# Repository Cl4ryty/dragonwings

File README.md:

# dragonwings
An ergonomic unibody split keyboard made for steno.

- key layout generated using 
- PCB design in KiCad
- uses  with 

## Features:
- for Pro Micro or compatible controllers
- choc spacing (for choc v1 switches)
- pcb backplate with holes for rubber feet and threaded insert – allows usage on desks as well as tripod mounting the keyboard
- approximate size: 31 x 11 x 2 cm
- 30 keys
  - 15 keys on each side
  - 3 thumb keys per side
  - for steno this means: 
    - 2 thumber keys (one per side)
    - split S and *: 2 S keys 4 * keys (2 per side)
    - 2 extra keys on the left, can be set arbitarily in firmware – for eample to switch between layers or used as modifier keys

## The built keyboard

### parts used:
- dragonwings pcb & backplate
- 30 pink choc switches (linear 20gf)
- 30 MCC keycaps
- Pro Micro
- 5 through hole rubber feet, 5mm diameter (search for glass table top spacers)
- 1 UNC 1/4" hex nut 
- 7 M2x5mm standoffs
- 14 M2x4mm screws
- 1 SMD button, 5x5x2mm
- 30 SMD diodes (1N4148W, SOD-123)

## repository file structure
- 
- `pretty_pictures` contains renders and images of the built keyboard
- `dragonwings_backplate` contains KiCAD files for the backplate as well as the gebers 
  – the dagonwings_backplate_gerbers are tested but are missing a hole for the 5th rubber foot without which the board is not stable on a flat surface
  – the dragonwings_backplate_gerbers_updated are genreated from the updated kicad files and contain the additional hole for the 5th foot – these have not been tested but should work and one then would not have to drill the hole manually
- the dragonwings kicad files are contained in the root directory and the corresponding gerbers (tested and working) are in the `dragonwings_gerbers` directory, also available as a zip archive
- `compiled firmware` contains compiled firmware without or with first-up chord-send and tap-and-hold chord repeat – they contain two layers, one steno layer using GeminiPR and a qwerty steno layer which can be toggled with the lower key of the leftmost column
- firmware files to modify and compile yourself are available [here](https://github.com/Cl4ryty/qmk-steno-extensions/tree/dragonwings/keyboards/dragonwings) (1up and repeat) and [here](https://github.com/Cl4ryty/qmk_firmware/tree/dragonwings/keyboards/dragonwings) (just QMK without steno extensions)

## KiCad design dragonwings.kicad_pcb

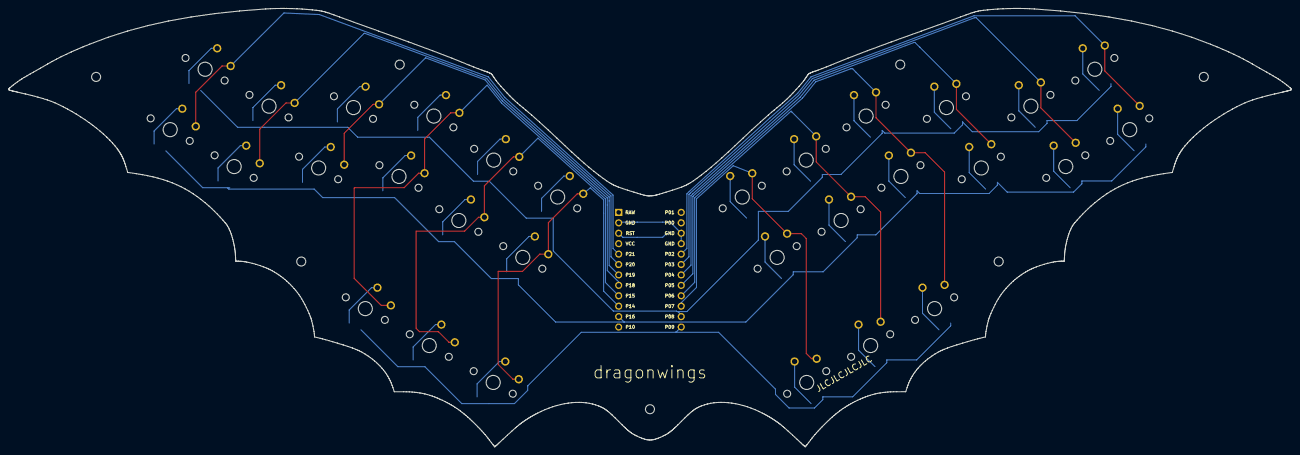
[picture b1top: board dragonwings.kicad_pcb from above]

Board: 2 copper layers, 312.8 x 106.9 mm, 69 parts (1 on the bottom side), 47 nets.

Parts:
B1: SW_TACT_ALPS_SKQGABE010
D1, D2, D3, D4, D5, D6, D7, D8, D9, D10, D11, D12, D13, D14, D15, D16, D17, D18, D19, D20, D21, D22, D23, D24, D25, D26, D27, D28, D29, D30: ComboDiode
MCU1: ProMicro
REF00, REF01, REF02, REF03, REF04, REF05, REF06: MountingHole_2.2mm_M2_DIN965
S1, S2, S3, S4, S5, S6, S7, S8, S9, S10, S11, S12, S13, S14, S15, S16, S17, S18, S19, S20, S21, S22, S23, S24, S25, S26, S27, S28, S29, S30: PG1350

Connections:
GND: B1.1, MCU1.2, MCU1.15, MCU1.16
P2: MCU1.17, S16.1, S17.1
P3: MCU1.18, S18.1, S19.1
P4: MCU1.19, S20.1, S21.1
P5: MCU1.20, S22.1, S23.1, S28.1
P6: MCU1.21, S24.1, S25.1, S29.1
P7: MCU1.22, S26.1, S27.1, S30.1
P8: D2.1, D4.1, D6.1, D8.1, D10.1, D12.1, D17.1, D19.1, D21.1, D23.1, D25.1, D27.1, MCU1.23
P9: D13.1, D14.1, D15.1, D28.1, D29.1, D30.1, MCU1.24
P14: MCU1.10, S11.1, S12.1, S15.1
P15: MCU1.9, S9.1, S10.1, S14.1
P16: D1.1, D3.1, D5.1, D7.1, D9.1, D11.1, D16.1, D18.1, D20.1, D22.1, D24.1, D26.1, MCU1.11
P18: MCU1.8, S7.1, S8.1, S13.1
P19: MCU1.7, S5.1, S6.1
P20: MCU1.6, S3.1, S4.1
P21: MCU1.5, S1.1, S2.1
RST: B1.2, MCU1.3
far_thumb: D15.2, S15.2
home_thumb: D14.2, S14.2
index_bottom: D9.2, S9.2
index_home: D10.2, S10.2
inner_bottom: D11.2, S11.2
inner_home: D12.2, S12.2
middle_bottom: D7.2, S7.2
middle_home: D8.2, S8.2
mirror_far_thumb: D30.2, S30.2
mirror_home_thumb: D29.2, S29.2
mirror_index_bottom: D24.2, S24.2
mirror_index_home: D25.2, S25.2
mirror_inner_bottom: D26.2, S26.2
mirror_inner_home: D27.2, S27.2
mirror_middle_bottom: D22.2, S22.2
mirror_middle_home: D23.2, S23.2
mirror_near_thumb: D28.2, S28.2
mirror_pinky1_bottom: D16.2, S16.2
mirror_pinky1_home: D17.2, S17.2
mirror_pinky2_bottom: D18.2, S18.2
mirror_pinky2_home: D19.2, S19.2
mirror_ring_bottom: D20.2, S20.2
mirror_ring_home: D21.2, S21.2
near_thumb: D13.2, S13.2
pinky1_bottom: D1.2, S1.2
pinky1_home: D2.2, S2.2
pinky2_bottom: D3.2, S3.2
pinky2_home: D4.2, S4.2
ring_bottom: D5.2, S5.2
ring_home: D6.2, S6.2

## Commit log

2022-07-25 ALL SORTS OF THINGS
2022-08-03 renamed renders and added photos
2022-08-22 cleaned up firmware and added versions with just 1up send and tap and hwold options
2022-08-22 Update README.md
    Added links to firmware
2022-10-09 Create assembly_instructions.md
    Added assembly instruction text
2022-10-09 Added link to assembly guide to README
